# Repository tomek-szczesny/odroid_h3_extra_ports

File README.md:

# odroid_h3_extra_ports

An add-on board for Odroid H3(+) with extra connectivity

- Fits into the H3(+) header directly, or with a ribbon cable.

- Has two M3 mounting holes

- 3x USB 2.0 ports with ESD and overcurrent protection (0.5A)

- 2x I2C ports compatible with Qwiic Connect System

- 1x RS-232 port with RTS/CTS (IDC-10, like on PC motherboards)

- 4-pin header for official power button with LED

- Optional resistor R1 for dimming the power button LED

The PCB is 4-layer, based on 1.6mm JLC7628 stackup.

More information here:

[H3 port extender, extra USB and RS-232 ports - ODROID](https://forum.odroid.com/viewtopic.php?f=172&t=45594)

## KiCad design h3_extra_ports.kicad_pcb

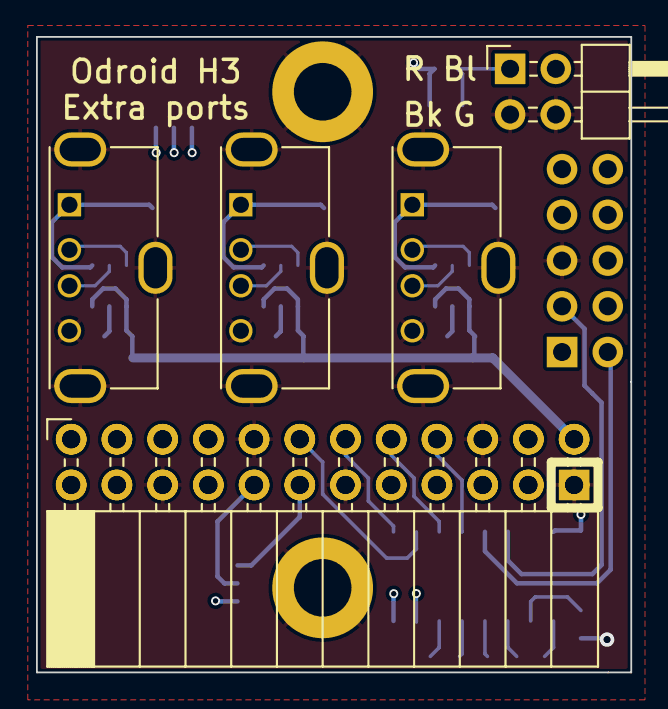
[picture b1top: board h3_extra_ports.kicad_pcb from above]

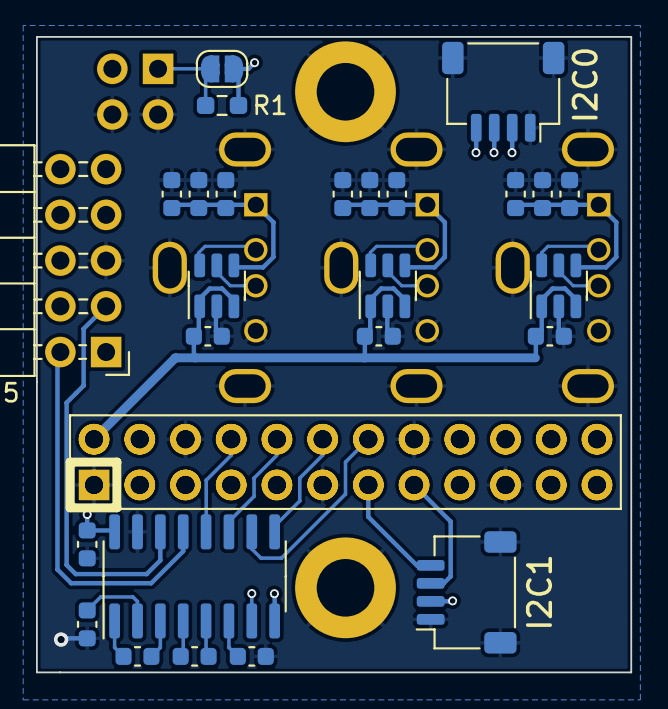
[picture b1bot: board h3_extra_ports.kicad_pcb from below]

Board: 4 copper layers, 33.0 x 35.3 mm, 34 parts (27 on the bottom side), 34 nets.

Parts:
C1, C3, C4, C5: 100n 16V; C_0603_1608Metric
C2: 1u 16V; C_0603_1608Metric
C6, C10, C14: 100n; C_0603_1608Metric
C7, C8, C9, C11, C12, C13, C15, C16, C17: 47u; C_0603_1608Metric
H1, H2: MountingHole_Pad; MountingHole_3.2mm_M3_DIN965_Pad
J1, J2, J3: USB_A; USB_A_Molex_105057_Vertical
J4: Conn_02x02_Odd_Even; PinHeader_2x02_P2.54mm_Horizontal
J5: RS232; PinHeader_2x05_P2.54mm_Horizontal
J6: Conn_02x12_Odd_Even; PinSocket_2x12_P2.54mm_Horizontal
J7, J8: Qwiik; JST_SH_SM04B-SRSS-TB_1x04-1MP_P1.00mm_Horizontal
J9: Conn_02x12_Odd_Even; PinHeader_2x12_P2.54mm_Vertical
JP1: Solder Jumper; SolderJumper-2_P1.3mm_Open_RoundedPad1.0x1.5mm
R1: DNI; R_0603_1608Metric_Pad0.98x0.95mm_HandSolder
U1: MAX3232; SOIC-16_3.9x9.9mm_P1.27mm
U2, U3, U4: TPD3S014; SOT-23-6

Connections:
/+3.3V_RUN_H: C2.2, J6.21, J7.2, J8.2, J9.4, JP1.2 (B), R1.2, U1.16 (VCC)
/+5V_RUN_H: C6.1, C10.1, C14.1, J6.23, J9.2, U2.1 (EN), U2.3 (IN), U3.1 (EN), U3.3 (IN), U4.1 (EN), U4.3 (IN)
/+V5P0A: J6.1, J9.24
/HDMI_CEC: J6.3, J9.22
/I2C_0_SCL: J6.7, J7.4, J9.18
/I2C_0_SDA: J6.5, J7.3, J9.20
/I2C_1_SCL: J6.12, J8.4, J9.13
/I2C_1_SDA: J6.10, J8.3, J9.15
/PWR_BTN#: J4.2, J6.8, J9.17
/RS232_CTS: J5.8, U1.8 (R2IN)
/RS232_RTS: J5.7, U1.7 (T2OUT)
/RS232_RX: J5.2, U1.13 (R1IN)
/RS232_TX: J5.3, U1.14 (T1OUT)
/UART0_CTS#: J6.13, J9.12, U1.9 (R2OUT)
/UART0_RTS#: J6.11, J9.14, U1.10 (T2IN)
/UART0_RXD: J6.17, J9.8, U1.12 (R1OUT)
/UART0_TXD: J6.15, J9.10, U1.11 (T1IN)
/USB2_P5_DN: J1.2 (D-), J6.16, J9.9, U2.6 (D2)
/USB2_P5_DP: J1.3 (D+), J6.18, J9.7, U2.5 (D1)
/USB2_P6_DN: J2.2 (D-), J6.2, J9.23, U3.6 (D2)
/USB2_P6_DP: J2.3 (D+), J6.4, J9.21, U3.5 (D1)
/USB2_P7_DN: J3.2 (D-), J6.20, J9.5, U4.6 (D2)
/USB2_P7_DP: J3.3 (D+), J6.22, J9.3, U4.5 (D1)
GND: C2.1, C4.1, C5.1, C6.2, C7.1, C8.1, C9.1, C10.2, C11.1, C12.1, C13.1, C14.2, C15.1, C16.1, C17.1, H1.1, H2.1, J1.4 (GND), J1.5 (Shield), J2.4 (GND), J2.5 (Shield), J3.4 (GND), J3.5 (Shield), J4.3, J4.4, J5.5, J6.6, J6.9, J6.14, J6.19, J6.24, J7.1, J7.MP (MountPin), J8.1, J8.MP (MountPin), J9.1, J9.6, J9.11, J9.16, J9.19, U1.15 (GND), U2.2 (GND), U3.2 (GND), U4.2 (GND)
unnamed: C1.1, U1.1 (C1+)
unnamed: C1.2, U1.3 (C1-)
unnamed: C3.1, U1.5 (C2-)
unnamed: C3.2, U1.4 (C2+)
unnamed: C4.2, U1.2 (VS+)
unnamed: C5.2, U1.6 (VS-)
unnamed: C8.2, C9.2, J1.1 (VBUS), U2.4 (OUT)
unnamed: C12.2, C13.2, J2.1 (VBUS), U3.4 (OUT)
unnamed: C16.2, C17.2, J3.1 (VBUS), U4.4 (OUT)
unnamed: J4.1, JP1.1 (A), R1.1

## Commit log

2022-11-26 Added production files
2022-12-23 Final design - first batch
